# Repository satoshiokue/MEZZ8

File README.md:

# MEZZ8
Z8 Mezzanine board for EMUZ80

R1 = 10k  
C1 = 0.1uF  

https://github.com/satoshiokue/EMUZ80-Z8  

MEZZ8専用プリント基板  
https://store.shopping.yahoo.co.jp/orangepicoshop/pico-a-063.html

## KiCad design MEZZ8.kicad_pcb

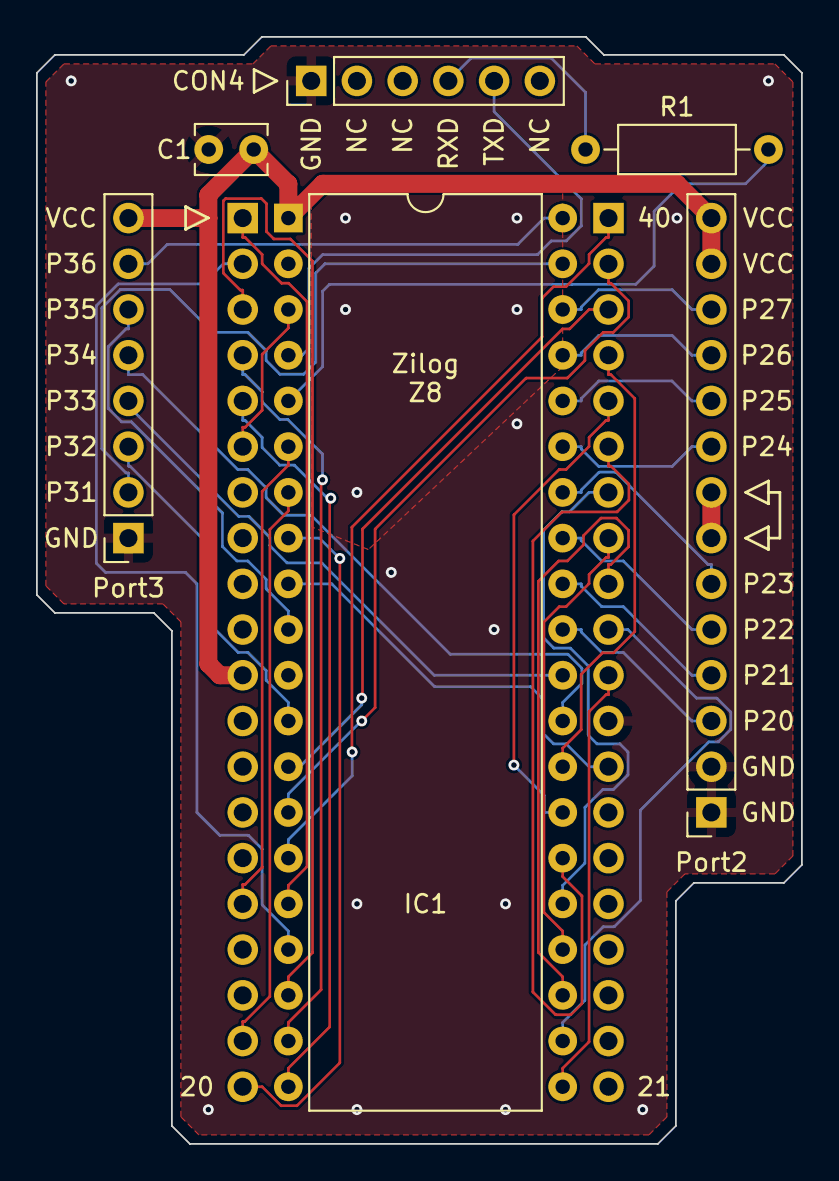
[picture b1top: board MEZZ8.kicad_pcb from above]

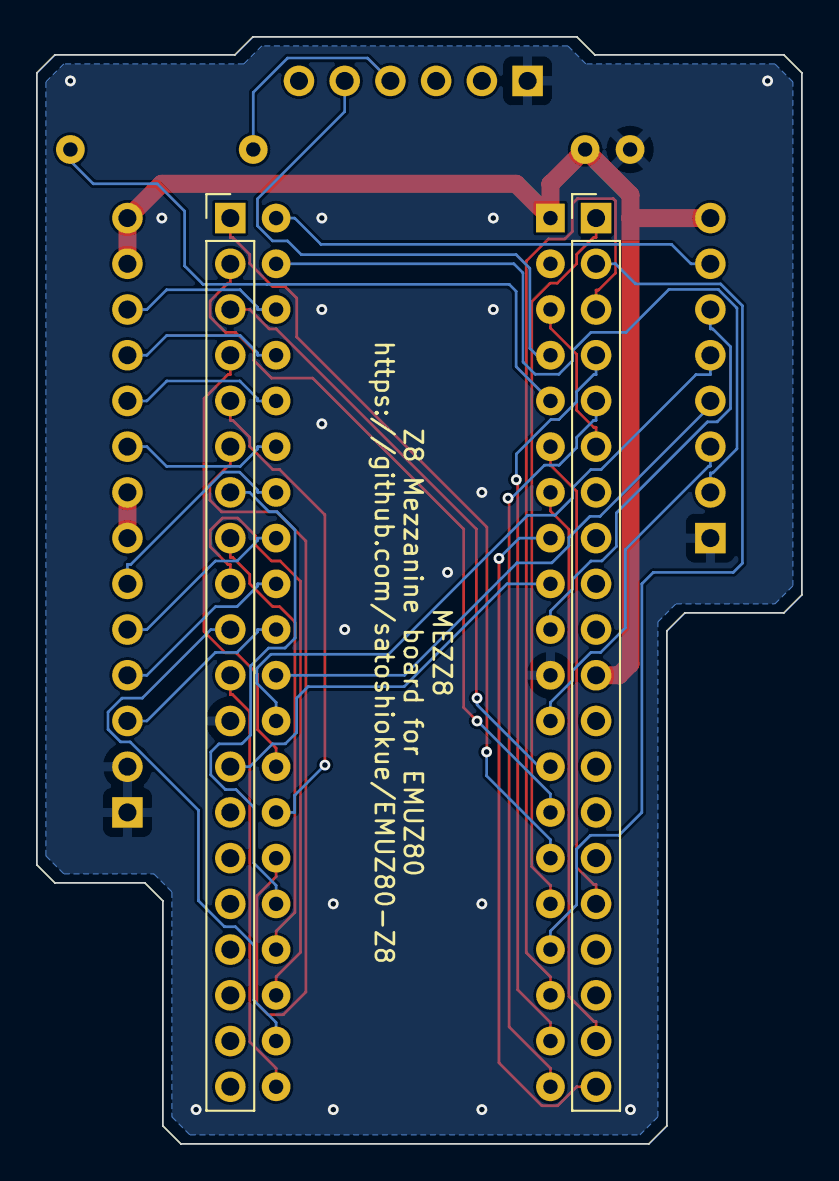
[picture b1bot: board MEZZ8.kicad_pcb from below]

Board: 2 copper layers, 42.5 x 61.5 mm, 8 parts (2 on the bottom side), 41 nets.

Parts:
C1: 0.1uF; C_Disc_D3.8mm_W2.6mm_P2.50mm
CON4: Conn_01x06; PinHeader_1x06_P2.54mm_Vertical
IC1: Z86C91-40-DIP; DIP-40_W15.24mm
J1, J2: Conn_01x20; PinHeader_1x20_P2.54mm_Vertical
Port2: Conn_01x14; PinSocket_1x14_P2.54mm_Vertical
Port3: Conn_01x08; PinSocket_1x08_P2.54mm_Vertical
R1: 10k; R_Axial_DIN0207_L6.3mm_D2.5mm_P10.16mm_Horizontal

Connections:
A0: IC1.21 (P10/AD0), J2.11
A1: IC1.22 (P11/AD1), J2.10
A2: IC1.23 (P12/AD2), J2.9
A3: IC1.24 (P13/AD3), J2.8
A4: IC1.25 (P14/AD4), J2.7
A5: IC1.26 (P15/AD5), J2.6
A6: IC1.27 (P16/AD6), J2.5
A7: IC1.28 (P17/AD7), J2.4
A8: IC1.13 (P00/A8), J2.3
A9: IC1.14 (P01/A9), J2.2
A10: IC1.15 (P02/A10), J2.1
A11: IC1.16 (P03/A11), J1.1
A12: IC1.17 (P04/A12), J1.2
A13: IC1.18 (P05/A13), J1.3
A14: IC1.19 (P06/A14), J1.4
A15: IC1.20 (P07/A15), J1.5
CLK: IC1.3 (XTAL1), J1.6
GND: C1.2, CON4.1, IC1.11 (GND), J2.12, Port2.1, Port2.2, Port3.1
unnamed: IC1.5 (RxD/P30), R1.2
unnamed: IC1.10 (P35), Port3.6
unnamed: IC1.12 (P32), Port3.3
unnamed: IC1.29 (P34/~DM), Port3.5
unnamed: IC1.30 (P33), Port3.4
unnamed: IC1.31 (P20), Port2.3
unnamed: IC1.32 (P21), Port2.4
unnamed: IC1.33 (P22), Port2.5
unnamed: IC1.34 (P23), Port2.6
unnamed: IC1.35 (P24), Port2.9
unnamed: IC1.36 (P25), Port2.10
unnamed: IC1.37 (P26), Port2.11
unnamed: IC1.38 (P27), Port2.12
unnamed: IC1.39 (P31/Tin), Port3.2
unnamed: IC1.40 (P36/Tout), Port3.7
unnamed: Port2.7, Port2.8
RXD: CON4.4, R1.1
R/~W: IC1.7 (R/~W), J1.19
TXD: CON4.5, IC1.4 (TxD/P37)
VCC: C1.1, IC1.1 (VCC), J1.11, Port2.13, Port2.14, Port3.8
~AS: IC1.9 (~AS), J2.13
~DS: IC1.8 (~DS), J1.20
~RESET: IC1.6 (~RESET), J1.16

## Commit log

2022-10-28 Create foo
